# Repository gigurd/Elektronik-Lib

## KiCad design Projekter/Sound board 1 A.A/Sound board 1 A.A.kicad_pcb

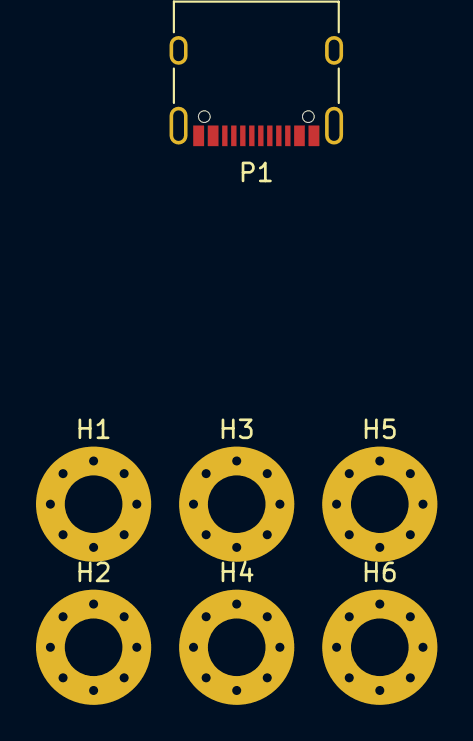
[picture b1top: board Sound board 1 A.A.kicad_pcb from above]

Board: 2 copper layers, 7 parts (0 on the bottom side), 2 nets, no tracks yet.

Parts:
H1, H2, H3, H4, H5, H6: MountingHole_Pad; MountingHole_3.2mm_M3_Pad_Via
P1: USB_C_Plug_USB2.0; USB_C_Receptacle_XKB_U262-16XN-4BVC11

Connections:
/PSU/VIN: P1.A4 (VBUS), P1.A9 (VBUS), P1.B4 (VBUS), P1.B9 (VBUS)
GND: H1.1, H2.1, H3.1, H4.1, H5.1, H6.1, P1.A1 (GND), P1.A12 (GND), P1.B1 (GND), P1.B12 (GND), P1.S1 (SHIELD)

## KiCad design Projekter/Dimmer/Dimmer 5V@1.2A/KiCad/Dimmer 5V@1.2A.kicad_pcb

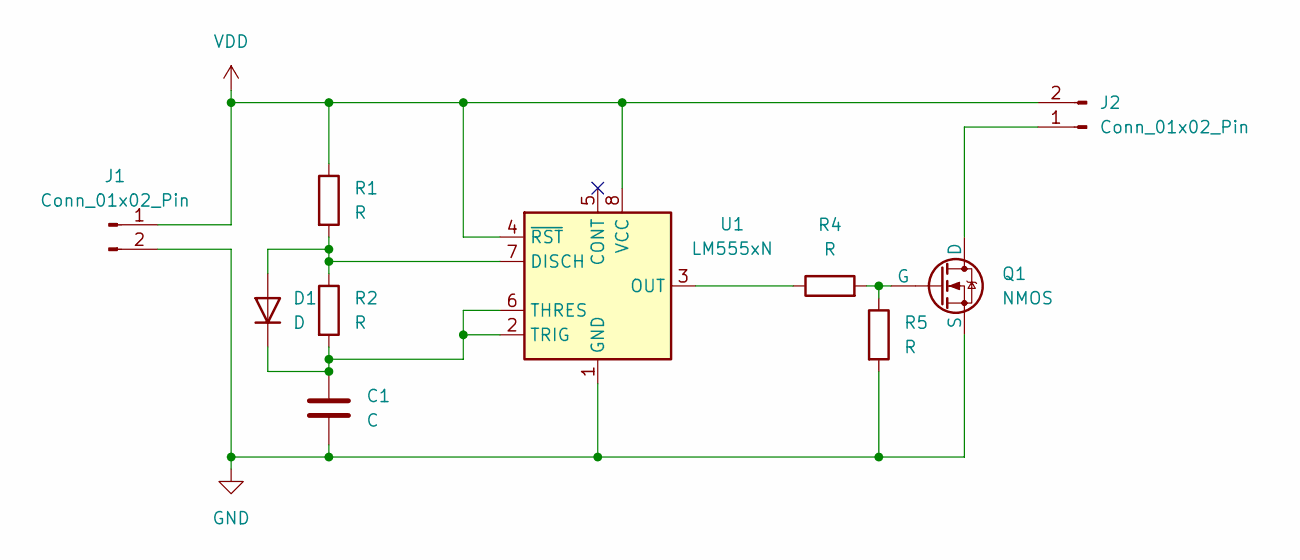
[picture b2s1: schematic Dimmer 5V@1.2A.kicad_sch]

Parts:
C1: C; C_Disc_D3.0mm_W1.6mm_P2.50mm
D1: D; D_DO-35_SOD27_P7.62mm_Horizontal
J1, J2: Conn_01x02_Pin; PinHeader_1x02_P2.54mm_Vertical
Q1: NMOS; TO-220-3_Vertical
R1, R2, R4, R5: R; R_Axial_DIN0204_L3.6mm_D1.6mm_P5.08mm_Horizontal
U1: LM555xN; DIP-8_W7.62mm

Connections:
GND: C1.2, J1.2, Q1.3 (S), R5.2, U1.1 (GND)
unnamed: D1.2 (A), R1.2, R2.1, U1.7 (DISCH)
unnamed: C1.1, D1.1 (K), R2.2, U1.2 (TRIG), U1.6 (THRES)
unnamed: J2.1, Q1.1 (D)
unnamed: Q1.2 (G), R4.2, R5.1
unnamed: R4.1, U1.3 (OUT)
VDD: J1.1, J2.2, R1.1, U1.4 (~RST), U1.8 (VCC)

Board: 2 copper layers, 10 parts (0 on the bottom side), 7 nets, no tracks yet.

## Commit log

2026-01-28 tilføjede mapper til QSPICE komponenter og kicad komponenter
2026-01-28 Komponenter fra MHM Lib er tilføjet
2026-01-29 Simulering af lys dæmper tilføjet
2026-01-29 tilføjet udregninger til NE555 timer
2026-01-29 Opdatering af Dimmer calculations
2026-01-29 KiCad project tilføjet
2026-02-02 Projekt noter oprettet, noter til sound board projekt lavet
2026-02-02 Projekt noter opdateret
2026-02-14 Project i kicad er oprettet og begyndt
